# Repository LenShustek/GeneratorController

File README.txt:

This is the hardware and software design for an external custom 
controller for Cummins standby power generators and transfer switches. 

We have a couple of these generators in locations which are unoccupied 
for long periods of time. The normal operation of the standard 
setup is to run the generator whenever the power is out, until 
either the power returns or the fuel runs out. 

What we want instead, when the property is not occupied, is for the 
generator to run enough to keep the food in the freezers cold, but not 
to run all the time. That conserves fuel, and annoys the neighbors less. 

Our custom controller works like this: after the power fails, it waits 
for a few hours to see if the power comes back. If it doesn't, it runs 
the generator for 30 minutes every few hours so that the freezers are 
kept cold. If someone is home and wants the power to be on all the time, 
there is an "at home" button on the front panel that does that. All the 
times are, of course, configurable. 

The controller also has a WiFi interface and acts as a web server, so 
you can use a browser from a remote location to check the status and 
make changes. (That depends, of course, on whether your location has 
internet access without utility power or when on generator power.) It 
can also send a text message and/or an email when power fails or is 
restored, using the IFTTT ("If This Then That") free service. 

Other features:
  - display of the utility and generator voltage levels (0-250 VAC)
  - display of the load current on each of two phases (0-100A)
  - display of the starter battery voltage after the power fails,
    when it is not being charged
  - a configurable generator exercise schedule
  - a realtime clock with battery backup
  - non-volatile memory for configuration information and an event log
  - a hardware watchdog timer that restarts the processor if something 
    locks up the controller
  - manual operation of the generator and transfer switch for testing
  
We have this installed and running with these two generator/switch configurations:
  - Cummins RS22 22 kW generator with the RA100A automatic transfer switch
    (smart generator, dumb switch)
  - Cummins RS30000 30 kW generator with the RSS100 automatic transfer switch "with controller"
    (dumb generator, smart switch)
  
See more information in the "design notes" file and in the source code comments.

This is a non-trivial amateur construction project, and the design here comes, of course,
with no guarantee that it will work for you. That said, we are happy with the way it 
works for us.

Len Shustek
December 2019

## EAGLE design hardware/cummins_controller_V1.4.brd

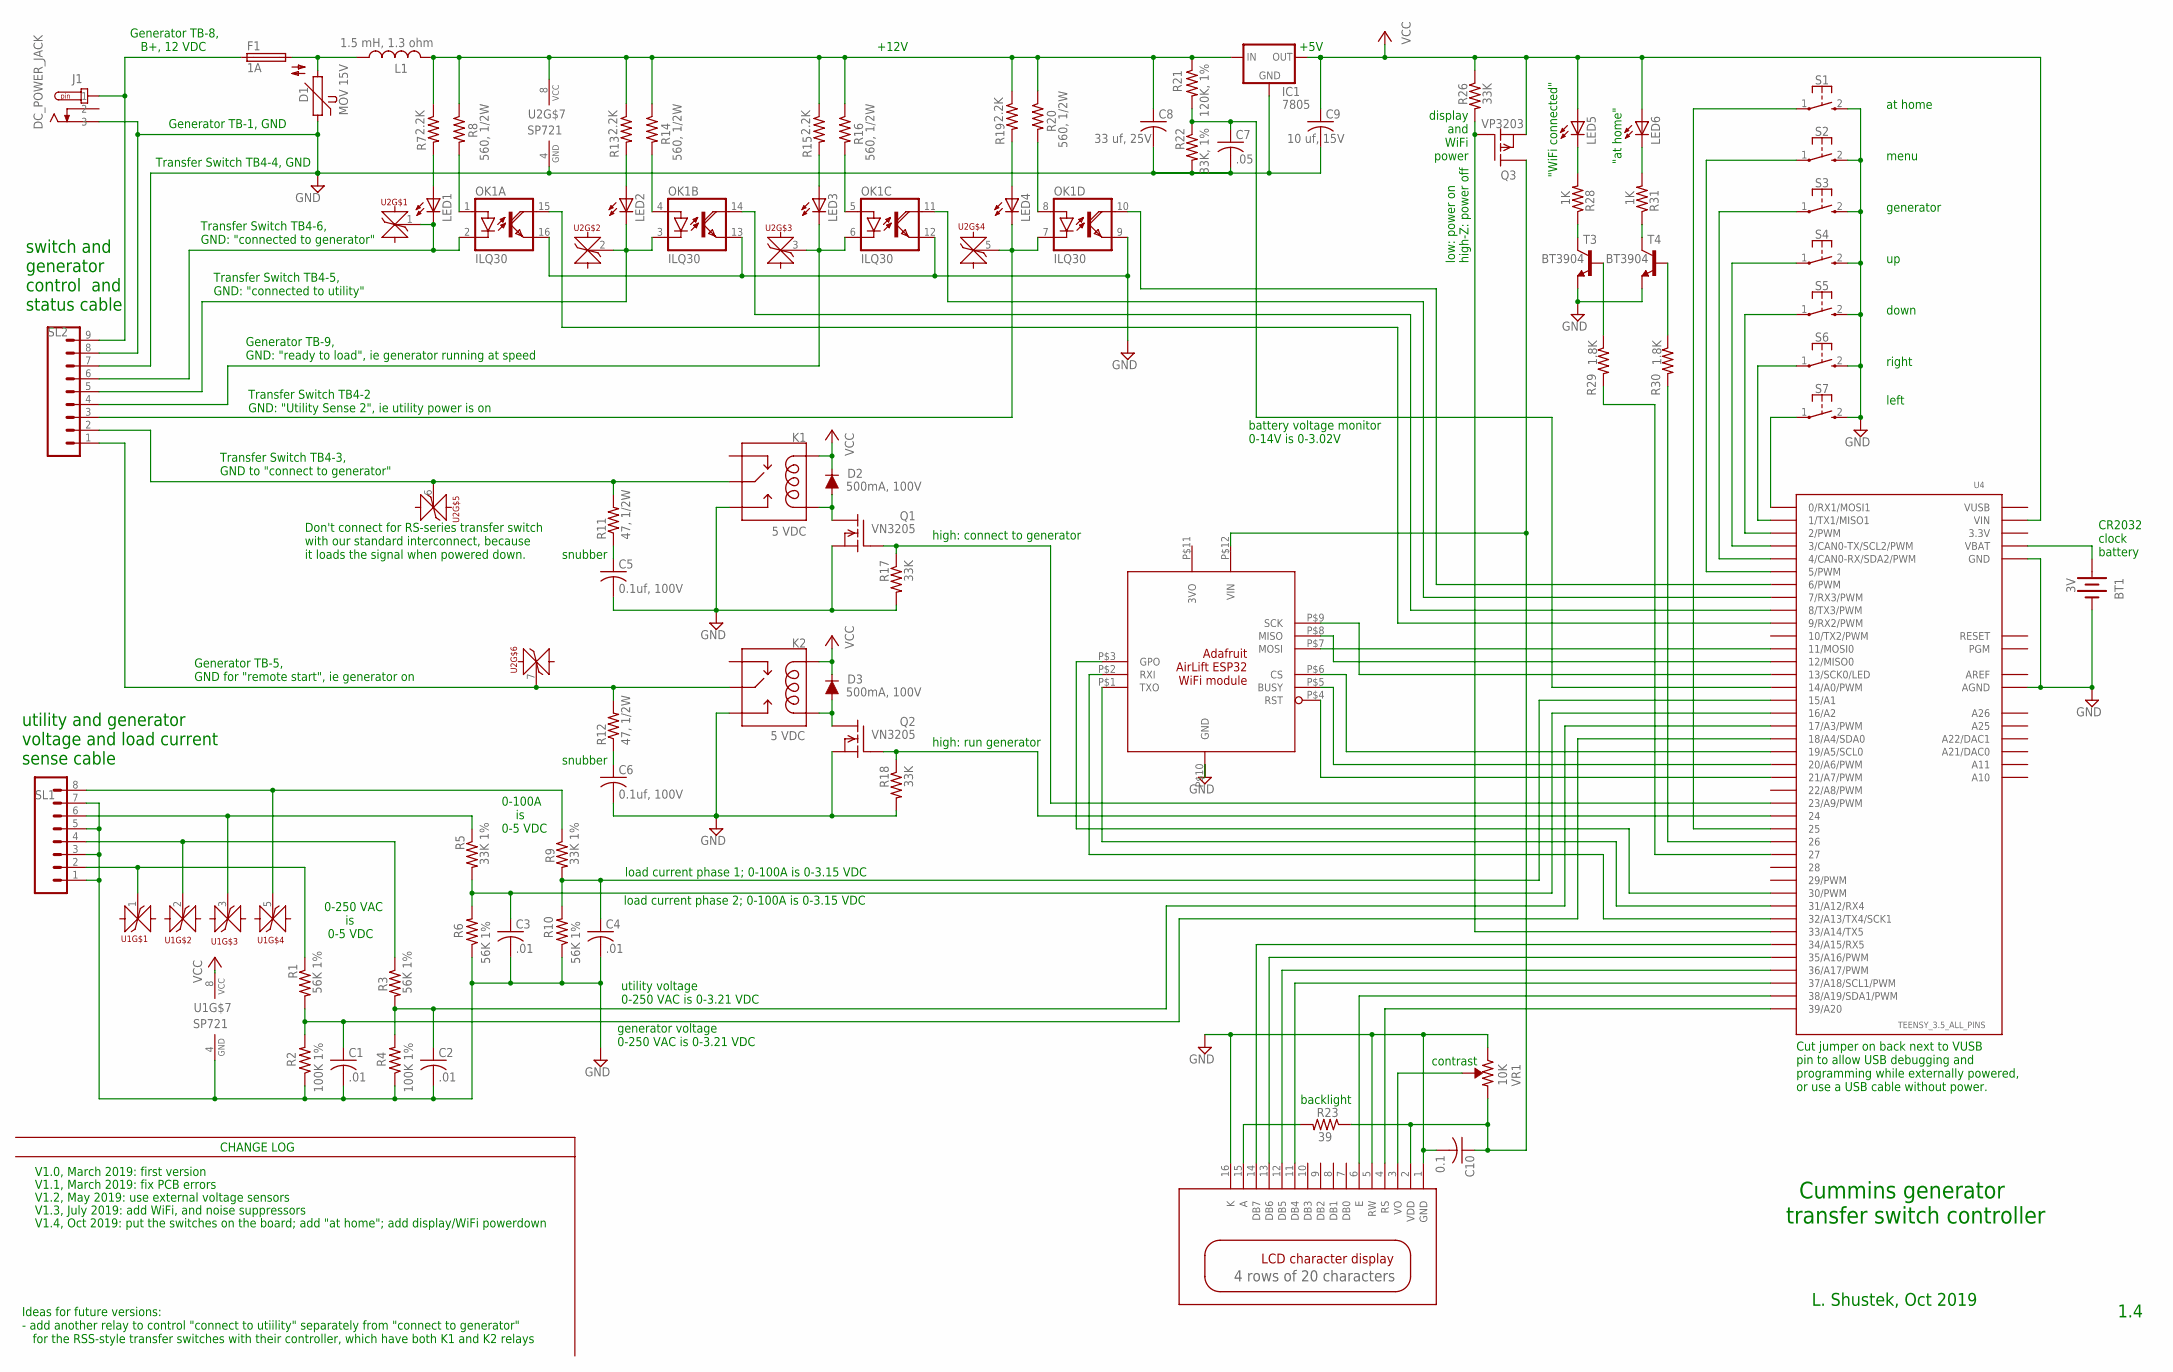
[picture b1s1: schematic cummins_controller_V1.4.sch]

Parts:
BT1: 3V; BATTCOM_20MM_PTH
C1, C2, C3, C4: .01; C0805K
C5, C6: 0.1uf, 100V; C1210K
C7: .05; C0805K
C8: 33 uf, 25V; C3216
C9: 10 uf, 15V; C1210K
C10: 0.1; C0805K
D1: MOV 15V; S14K230
D2, D3: 500mA, 100V; SOD-323
F1: 1A; PICOFUSE
IC1: 7805; 78XXS
J1: DC_POWER_JACK
K1, K2: 5 VDC; RELAY-PANASONIC-JS
L1: 1.5 mH, 1.3 ohm; INDUCTOR_1.1IN
LED1, LED2, LED3, LED4, LED5, LED6: LED5MM
OK1: ILQ30; DIL16
Q1, Q2: VN3205; SOT89
Q3: VP3203; SOT89
R1, R3, R6, R10: 56K 1%; M1206
R2, R4: 100K 1%; M1206
R5, R9: 33K 1%; M1206
R7, R13, R15, R19: 2.2K; M1206
R8, R16, R20: 560, 1/2W; R1210
R11, R12: 47, 1/2W; R1210
R14: 560, 1/2W; R1210W
R17, R18, R26: 33K; M1206
R21: 120K, 1%; M1206
R22: 33K, 1%; M1206
R23: 39; M1206
R28, R31: 1K; M1206
R29, R30: 1.8K; M1206
S1, S2, S3, S4, S5, S6, S7: PUSHBUTTON-SPST
SL1: M08; 08P
SL2: M09; 09P
T3, T4: BT3904; SOT23-3
U1, U2: SP721; TVS_6DIODE_ARRAY
U3: ADAFRUIT_AIRLIFT_ESP32
U4: TEENSY_3.5_ALL_PINS
VR1: 10K; TRIMBOT-BOURNS-3362M
X1: 4 rows of 20 characters; LCD-CHARACTER-DISPLAY-20X4

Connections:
3.3V: U4.3.3V, U4.3.3V3 (3.3V), U4.3.3V4 (3.3V)
AREF: U4.AREF
GND: BT1.2 (-), C1.2, C2.2, C3.2, C4.2, C5.2, C6.2, C7.2, C8.2, C9.2, C10.2, D1.1, IC1.GND, J1.P$5 (3), K1.P$3 (NO), K2.P$3 (NO), OK1.9 (EMI), OK1.12 (EMI), OK1.13 (EMI), OK1.16 (EMI), Q1.3 (S), Q2.3 (S), R2.1, R4.1, R6.1, R10.1, R17.2, R18.2, R22.2, S1.2 (3), S2.2 (3), S3.2 (3), S4.2 (3), S5.2 (3), S6.2 (3), S7.2 (3), SL1.1, SL1.3, SL1.5, SL1.7, SL2.7, SL2.8, T3.2 (E), T4.2 (E), U1.4 (GND), U2.4 (GND), U3.P$10 (GND), U4.AGND, U4.GND, U4.GND1 (GND), U4.GND3 (GND), U4.GND4 (GND), U4.GND6 (GND), VR1.3 (CW), X1.1 (GND), X1.5 (RW), X1.16 (K)
unnamed: BT1.1 (+), U4.VBAT
unnamed: D2.A, K1.P$5 (COIL2), Q1.2 (D), Q1.2@1 (D)
unnamed: S7.1, U4.0 (0/RX1/MOSI1)
unnamed: LED1.A, R7.2
unnamed: R9.1, SL1.8, U1.5
unnamed: D3.A, K2.P$5 (COIL2), Q2.2 (D), Q2.2@1 (D)
unnamed: U3.P$1 (TXO), U4.31/A12 (31/A12/RX4)
unnamed: LED2.K (C), OK1.3 (C), SL2.5, U2.2
unnamed: F1.1, J1.P$1 (1), SL2.9
unnamed: LED2.A, R13.2
unnamed: K2.P$1 (MAIN), R12.2, SL2.1, U2.7
unnamed: K1.P$1 (MAIN), R11.2, SL2.2, U2.6
unnamed: LED3.A, R15.2
unnamed: Q2.1 (G), R18.1, U4.24
unnamed: C4.1, R9.2, R10.2, U4.15/A1
unnamed: R5.1, SL1.6, U1.3
unnamed: C3.1, R5.2, R6.2, U4.16/A2
unnamed: R3.1, SL1.4, U1.2
unnamed: C2.1, R3.2, R4.2, U4.17/A3 (17/A3/PWM)
unnamed: LED4.A, R19.2
unnamed: OK1.5 (A), R16.2
unnamed: R1.1, SL1.2, U1.1
unnamed: R30.1, T4.1 (B)
unnamed: LED1.K (C), OK1.2 (C), SL2.6, U2.1
unnamed: C1.1, R1.2, R2.2, U4.18/A4 (18/A4/SDA0)
unnamed: U3.P$9 (SCK), U4.13 (13/SCK0/LED)
unnamed: U3.P$8 (MISO), U4.12 (12/MISO0)
unnamed: U3.P$7 (MOSI), U4.11 (11/MOSI0)
unnamed: U3.P$6 (CS), U4.19/A5 (19/A5/SCL0)
unnamed: U3.P$5 (BUSY), U4.20/A6 (20/A6/PWM)
unnamed: U3.P$4 (RST), U4.21/A7 (21/A7/PWM)
unnamed: U3.P$2 (RXI), U4.32/A13 (32/A13/TX4/SCK1)
unnamed: U4.34/A15 (34/A15/RX5), X1.14 (DB7)
unnamed: R31.1, T4.3 (C)
unnamed: U4.39/A20, X1.4 (RS)
unnamed: U4.38/A19 (38/A19/SDA1/PWM), X1.6 (E)
unnamed: LED3.K (C), OK1.6 (C), SL2.4, U2.3
unnamed: U4.37/A18 (37/A18/SCL1/PWM), X1.11 (DB4)
unnamed: U4.36/A17 (36/A17/PWM), X1.12 (DB5)
unnamed: U4.35/A16 (35/A16/PWM), X1.13 (DB6)
unnamed: Q1.1 (G), R17.1, U4.23/A9 (23/A9/PWM)
unnamed: C8.1, IC1.IN, L1.P$2 (2), R7.1, R8.1, R13.1, R14.1, R15.1, R16.1, R19.1, R20.1, R21.1, U2.8 (VCC)
unnamed: S6.1, U4.1 (1/TX1/MISO1)
unnamed: S5.1, U4.2 (2/PWM)
unnamed: S4.1, U4.3 (3/CAN0-TX/SCL2/PWM)
unnamed: S3.1, U4.4 (4/CAN0-RX/SDA2/PWM)
unnamed: S2.1, U4.5 (5/PWM)
unnamed: VR1.2 (WIPER), X1.3 (VO)
unnamed: R23.2, X1.15 (A)
unnamed: S1.1, U4.25
unnamed: LED5.K (C), R28.2
unnamed: OK1.10 (COL), U4.6 (6/PWM)
unnamed: OK1.11 (COL), U4.7 (7/RX3/PWM)
unnamed: OK1.14 (COL), U4.8 (8/TX3/PWM)
unnamed: OK1.15 (COL), U4.9 (9/RX2/PWM)
unnamed: C5.1, R11.1
unnamed: C6.1, R12.1
unnamed: OK1.1 (A), R8.2
unnamed: LED4.K (C), OK1.7 (C), SL2.3, U2.5
unnamed: OK1.4 (A), R14.2
unnamed: LED6.K (C), R31.2
unnamed: OK1.8 (A), R20.2
unnamed: C7.1, R21.2, R22.1, U4.14/A0 (14/A0/PWM)
unnamed: Q3.1 (G), R26.2, U4.33/A14 (33/A14/TX5)
unnamed: U3.P$3 (GPO), U4.30 (30/PWM)
unnamed: R29.1, T3.1 (B)
unnamed: R28.1, T3.3 (C)
unnamed: R29.2, U4.27
unnamed: D1.2, F1.2, L1.P$1 (1)
unnamed: R30.2, U4.26
VCC: C9.1, D2.C, D3.C, IC1.OUT, K1.P$2 (COIL1), K2.P$2 (COIL1), LED5.A, LED6.A, Q3.3 (S), R26.1, U1.8 (VCC), U4.VIN
VDD: C10.1, Q3.2 (D), Q3.2@1 (D), R23.1, U3.P$12 (VIN), VR1.1 (CCW), X1.2 (VDD)
VUSB: U4.VUSB

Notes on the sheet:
utility voltage 0-250 VAC is 0-3.21 VDC
generator voltage 0-250 VAC is 0-3.21 VDC
Cummins generator transfer switch controller
L. Shustek, Oct 2019
backlight
+5V
1.4
CR2032 clock battery
contrast
Transfer Switch TB4-5, GND: "connected to utility"
Generator TB-8, B+, 12 VDC
Transfer Switch TB4-4, GND
Generator TB-1, GND
Transfer Switch TB4-6, GND: "connected to generator"
Generator TB-5, GND for "remote start", ie generator on
Transfer Switch TB4-3, GND to "connect to generator"
Generator TB-9, GND: "ready to load", ie generator running at speed
high: run generator
high: connect to generator
switch and generator control and status cable
utility and generator voltage and load current sense cable
load current phase 1; 0-100A is 0-3.15 VDC
load current phase 2; 0-100A is 0-3.15 VDC
0-100A is 0-5 VDC
battery voltage monitor 0-14V is 0-3.02V
snubber
Transfer Switch TB4-2 GND: "Utility Sense 2", ie utility power is on
0-250 VAC is 0-5 VDC
CHANGE LOG
V1.0, March 2019: first version
V1.1, March 2019: fix PCB errors
V1.2, May 2019: use external voltage sensors
V1.3, July 2019: add WiFi, and noise suppressors
Cut jumper on back next to VUSB pin to allow USB debugging and programming while externally powered, or use a USB cable without power.
"WiFi connected"
V1.4, Oct 2019: put the switches on the board; add "at home"; add display/WiFi powerdown
low: power on high-Z: power off
display and WiFi power
+12V
"at home"

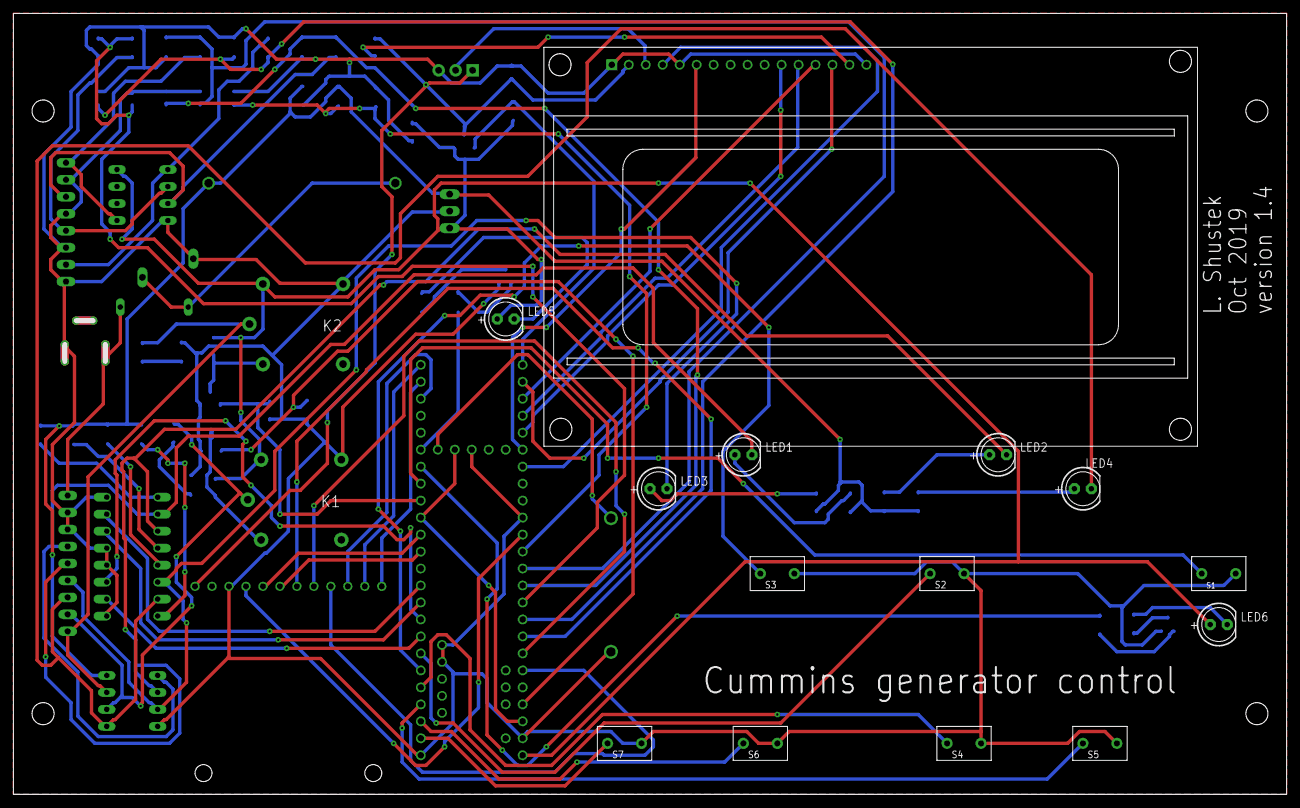
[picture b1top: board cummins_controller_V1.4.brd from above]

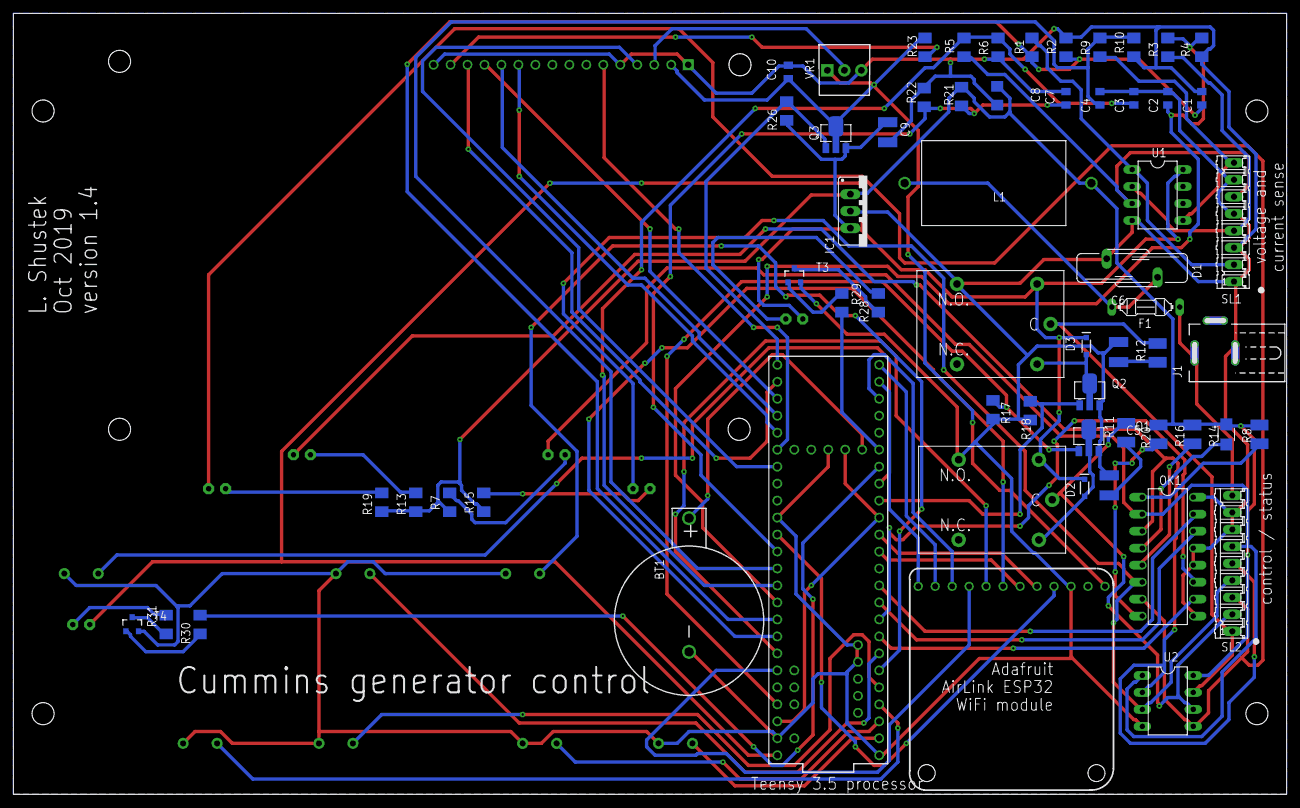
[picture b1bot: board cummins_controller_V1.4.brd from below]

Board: 2 copper layers, 189.7 x 116.1 mm, 75 parts (61 on the bottom side), 74 nets.

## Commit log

2020-01-01 Cummins generator controller
2021-11-14 retry IFTTT, sort visitor history by date, power cycle WiFi when it won't start

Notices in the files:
parts and their libraries:
SparkFun-Batteries: Licensing: Creative Commons ShareAlike 4.0 International - https://creativecommons.org/licenses/by-sa/4.0
